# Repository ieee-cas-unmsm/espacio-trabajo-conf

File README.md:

# Configuración de entorno - Septiembre 2024
Realizando modificaciones de prueba
### **Objetivos**  
> Entender la dinámica de trabajo grupal con GitHub  
> Aprender diseño de circuito impreso en KiCAD 
> Compilar y subir codigo C a microcontroladores AVR  

## Tabla de Contenidos

1. [Instalación WSL](#instalacion-WSL)
2. [Manejando la Terminal](#manejando-la-terminal)

## Instalación WSL (Windows Subsystem for Linux)
¿Nos cambiamos de sistema operativo? No. Estaremos utilizando una distribución de Linux, que es Ubuntu, dentro de Windows. La razones para hacerlos son muchas, pero, poniendolo en pocas puntos:
- Permite usar las herramientas de Linux en Windows
- Facilitará la instalación de programas a una sola linea de comando.
- Los paquetes y entorno de instalación son homogeneos.

### WSL / Ubuntu
- Ingresamos a *Powershell*, ejecutamos como administrador y ejecutamos el siguiente comando para instalar WSL 2:
```
wsl --install
```
- Terminada la isntalación de WSL 2, instalaremos Ubuntu con el siguiente comando:
```
wsl --install -d Ubuntu
```

## Comandos en la Terminal
A diferencia de Windows nuestra forma de interactuar con Ubuntu será unicamente mediante la terminal, es decir lineas de comando. Para ello es necesario saber los comandos básicos para la manipulación de carpetas y ficheros.
> Todas las acciones que se realizan se llevan acabo en la dirección actual.

### Manipulación de carpetas y ficheros
- Para ver las carpetas y ficheros visibles del directorio actual, ejecutaremos el comando:
```
ls
```
- Para ver las carpetas y ficheros **NO** visibles del directorio actual, ejecutaremos el comando:
```
la
```
> Si agregamos -l despues del comando podremos visualizar los archivos de forma vertical.

### Manipulación de carpetas y ficheros
Comandos empleados para la visualización, creación, modificación y eliminación de los archivos

- Comandos para la creación de una carpeta y archivo
  ```
  mkdir carpeta_creada          
  ```
  ```
  touch archivo_creado.txt
  ```
  > Se crearán en el directorio actual

- Comandos para mover carpetas o ficheros hacia otra dirección
    > Preparación de las carpetas y archivos para probar los comandos
  ```
  cd
  mkdir carpeta_destino
  mkdir carpeta_fuente
  cd carpeta_fuente
  touch archivo_mover.txt
  cd
  ```
    > Comando para mover
  ```
  mv carpeta_fuente/archivo_mover.txt carpeta_destino
  ```
    > Revisamos la carpeta con el archivo movido
  ```
  ls carpeta_destino
  ```
- Comandos para copiar una carpeta o fichero a otra dirección.
    > Preparación de las carpetas y archivos para probar los comandos
  ```
  cd
  mkdir carpeta_destino_A
  cd carpeta_destino_A
  mkdir carpeta_destino_B
  cd carpeta_destino_B
  mkdir carpeta_destino_C
  cd mkdir carpeta_destino_C
  touch archivo_copiar_1.txt
  touch archivo_copiar_2.c
  touch archivo_copiar_3.cpp
  cd
  ```
    > Copiando la carpeta carpeta_destino_C al directorio principal
  ```
  cd carpeta_destino_A/carpeta_destino_B
  cp -r carpeta_destino_C $HOME
  ```
    > Copiando el archivo_copiar_1.txt a carpeta_destino_B
  ```
  cp archivo_copiar_1.txt ../
  ```

Comandos para la eliminación de carpetas y archivos:
> Eliminamos la carpeta y los archivos dentro de la misma
```
rm -r carpeta_creada
```

## Git
Ahora iniciaremos con el control de versiones GIT y los repositorios existentes en GITHUB. 
Aclararemos que utilizaremos git tanto en Windows como en Ubuntu, se espcificará antes en cual de los entornos estamos trabajando.

### Git - WSL / Ubuntu
Iniciaremos en el entorno que trabajamaos previamente, para comprobar la isntalación de Git dentro de ubuntu ejecutamos el comando:
> De forma nativa Linux incluye Git, GCC, entre otras herramientas que utilizaremos
```
git --version
```

Ahora deberemos de configurar nuestro nombre y correo que emplearemos
```
git config --global user.name "nombre_cuenta"
git config --global user.email "correo_cuenta"
```
### Comandos en el Control de Versiones
Para facilitar algunas actividades instalaremos 2 paquetes: *gedit* y *VScode*
> Primero revisaremos las actualizaciones de los paquetes instalados
```
sudo apt update
```
> Actualizaremos aquellos paquetes que tienen cambios
```
sudo apt upgrade
```

> Instalamos el paquete geddit en el entorno
```
sudo apt install geddit
```
> Instalaremos de forma no convencional VS code
```
code .
```
> Modificaremos el nombre por defecto de la rama principal
```
git config --global init.defaultBranch main
```

### Usando Git
Github no es lo mismo a Git, es cierto que comparten comandos y funcionalidad pero, es debido a que GitHub es una plataforma desarrollada en base al Git y que opera utiliza sus comandos. Ahora nos centraremos en revisar el flujo de trabajo en archivos locales. 
- Crearemos e ingresamos a la carpeta donde haremos las modificaciones
  ```
  cd
  mkdir git_local
  cd git_local
  ```
- Inicializaremos git dentro de la carpeta de trabajo
  > Podemos usar el comando la -l para visualizar la carpeta no visible creada .git
  ```
  git init
  la -l
  ```
- Crearemos un archivo y una carpeta
  ```
  mkdir primera_carpeta
  touch primer_archivo.c
  ```
- Revisaremos el estado actual de nuestra carpeta inicializada
  > Observaremos que existen archivos no "trackeados", es decir sin seguimiento para el control de versiones
  ```
  git status
  ```
- Aggregaremos ambos archivos al flujo de git
  > Al emplear add . implica que todos los archivos de la dirección pasan a ser trackeados
  > Para deshacer se emplea git reset para eliminar a los archivos del track
  ```
  git add .
  ```

- Commit a los archivos agregados al git
  Lo primero por definir es que la etapa del commit no se realiza en cada momento o de forma repetitiva, si no se busca crear commit en puntos claves del desarrollo de nuestro proyecto.
  > Al ser nuestro primer commit será el punto máximo de retorno
  > -m es la indicación que será un mensaje breve
  ```
  git commit -m "Añadi el archivo primer_archivo y el directorio primera_carpeta"
  ```
- Verificamos nuestra rama principal
  > Las ramas en GIT hacen referencia espacios de trabajo independientes, siendo main la principal / official del proyecto
  ```
  git status
  ```

- Modificación de archivos
  > Modificaremos el contenido del archivo primer_archivo.c
  ```
  gedit primer_archivo.c
  ```
  > Se abrirá una nueva ventano donde codificaremos lo siguiente, mas adelante compilaremos y ejecutaremos.
  ```
  #include <stdio.h>
  int main(){
	  for (int i=0; i<10;i++){
		  printf("%d\n",i);
	  }
  }
  ```
  Ingresaremos a primera_carpeta y añadiremos un documento de texto
  > Ingresa al documento utilizando *vim* o *nano* y modifica su contenido
  ```
  cd primera_carpeta
  touch documento.txt
  ```
  Observaremos los cambios en el control de versiones
  > Describirá los cambios ocurridos
  ```
  git status
  ```
  Añadiremos y Commitearemos el desarrollo
  ```
  git add .
  git commit -m "Modificación primer_archivo y nuevo archivo en carpeta"
  ```
- Creación de una nueva branch (rama)
  Las ramas son empleadas para hacer cambios seguros al documento oficial. Debido a que se crea una copia identica de los documentos trackeados.
  > Creamos una branch llamada nueva_rama y nos movemos usando checkout
  ```
  git branch rama_nueva
  git checkout rama_nueva
  ```
  > Podemos simplificar cuando recien la crearemos
  ```
  git branch -b rama_nueva
  ```
  Modificaremos el documento primer_documento.c de la siguietne forma:
  > Recordar que debemos de ingresar utilizando algun visor de texto
  ```
  #include <stdio.h>
  int main(){
	  for (int i=0; i<10;i++){
		  printf("%d\n",i*i);
	  }
  }
  ```
  Agregaremos un nuevo archivo dentro de la carpeta y tambien modificaremos el existente
  > Nuevo archivo
  ```
  touch documento2.txt
  ```
  > Modificar archivo
  ```
  Hola esta es una modificacion en la branch: nueva_rama
  ```
  Repetiremos el proceso de añadir y commit
- Moviendonos entre commits
  Una gran funcionalidad de git es el hecho de que todo lo que has realizado puede recuperarse. Restaurar versiones anteriores, explorar ramas y juntarlas o merge, que veremos mas adelante.
  > Visualizamos
  ```
  git log
  ```
  > Visualización mas ordenada
  ```
  git log --oneline
  ```
  Para saltar entre los commits podemos emplear las primeras letras identificadores de cada branch
  > En este caso puede que cada uno tenga un número diferente, estar atento.
  ```
  git checkout "segundo commit numero"
  ```
  Revisar la lista de los commit realizados, bueno ahora unicamente tenemos el anterior. Los cambios superiro no estan disponibles para observarlos, sin embargo, podemos dirigirnos ahí.
  > Revisamos los commits disponibles
  ```
  git log --oneline
  ```
  > Regresamos a nuestro commit inicial
  ```
  git 
  ```
- Merge y culminación de una rama
  Finalmente, la ultima parte antes de llegar al KiCAD y parte de la programación es entender a fusionar estos cambios
  > Nos situaremos en la rama main (principal) y en el último commit
  ```
  git checkout main
  git checkout "ultimo_commit"
  ```
  Realizamos el proceso de merge con la branch: "rama_nueva"
  > Consideraciones
  ```
  git merge rama_actual rama_nueva
  ```
  > Deberemos de solucionar los problemas
  Finalmente exploramos los archivos y observamos los cambios jiji

## KiCAD
Para ello cada uno de nosotros trabajaremos en un archivo del

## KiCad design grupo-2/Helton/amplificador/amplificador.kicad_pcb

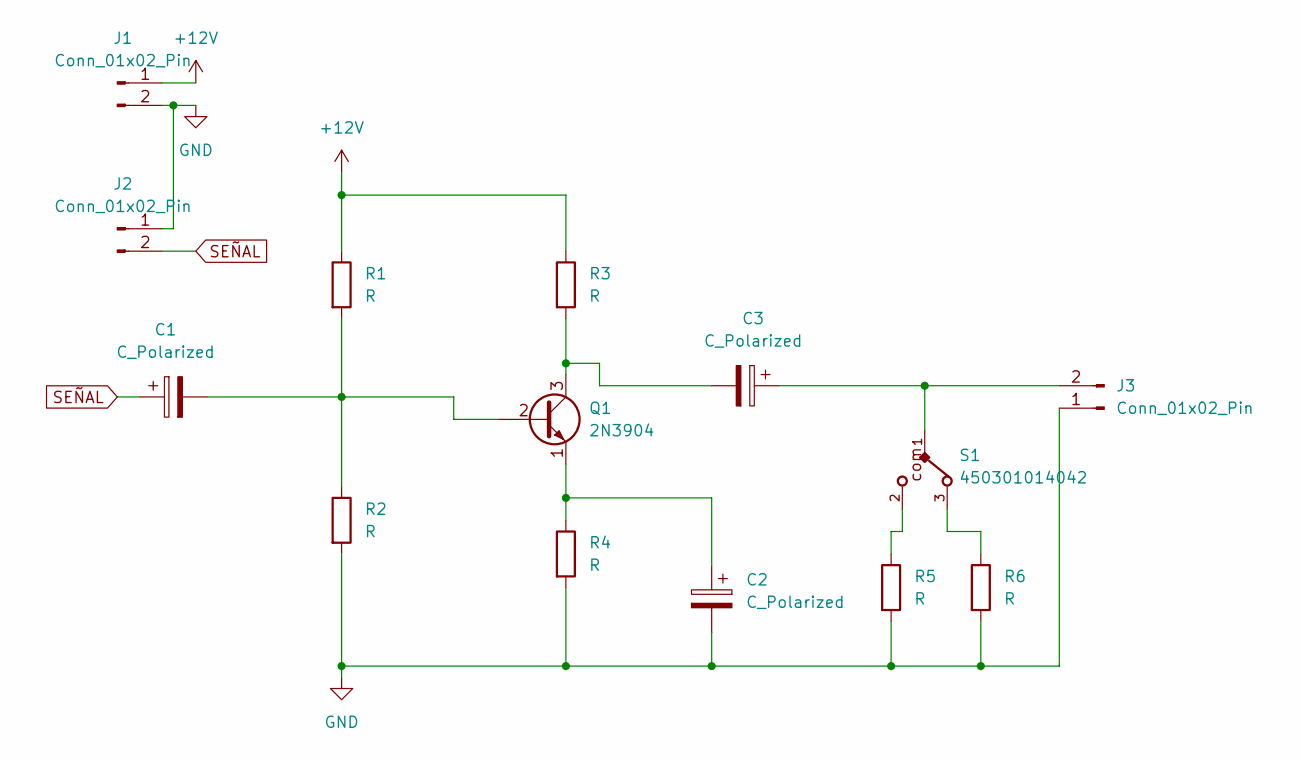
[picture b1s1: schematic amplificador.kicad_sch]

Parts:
C1, C2, C3: C_Polarized; CP_Radial_D6.3mm_P2.50mm
J1, J2, J3: Conn_01x02_Pin; PinHeader_1x02_P2.54mm_Vertical
Q1: 2N3904; TO-92_Inline
R1, R2, R3, R4, R5, R6: R; R_Axial_DIN0207_L6.3mm_D2.5mm_P10.16mm_Horizontal
S1: 450301014042; PART-NUMBER 450301014042

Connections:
+12V: J1.1, R1.1, R3.1
GND: C2.2, J1.2, J2.1, J3.1, R2.2, R4.2, R5.2, R6.2
unnamed: C3.1, J3.2, S1.1
unnamed: C1.2, Q1.2 (B), R1.2, R2.1
unnamed: C3.2, Q1.3 (C), R3.2
unnamed: C2.1, Q1.1 (E), R4.1
unnamed: R5.1, S1.2
unnamed: R6.1, S1.3
SEÑAL: C1.1, J2.2

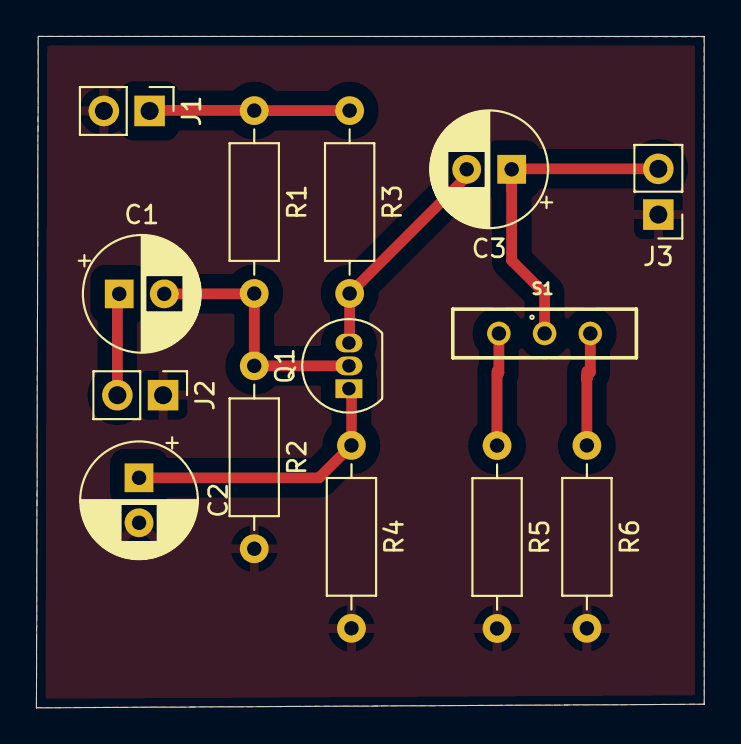
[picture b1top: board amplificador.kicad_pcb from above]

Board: 2 copper layers, 37.1 x 37.3 mm, 14 parts (0 on the bottom side), 9 nets.

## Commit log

2024-10-05 Actividades grupo 1
2024-10-05 avance bryan, actividad 1 fin
2024-10-06 grupo 2 domingoo 6
2024-10-06 Actividad Virtual Final
2025-08-30 test_ssh
